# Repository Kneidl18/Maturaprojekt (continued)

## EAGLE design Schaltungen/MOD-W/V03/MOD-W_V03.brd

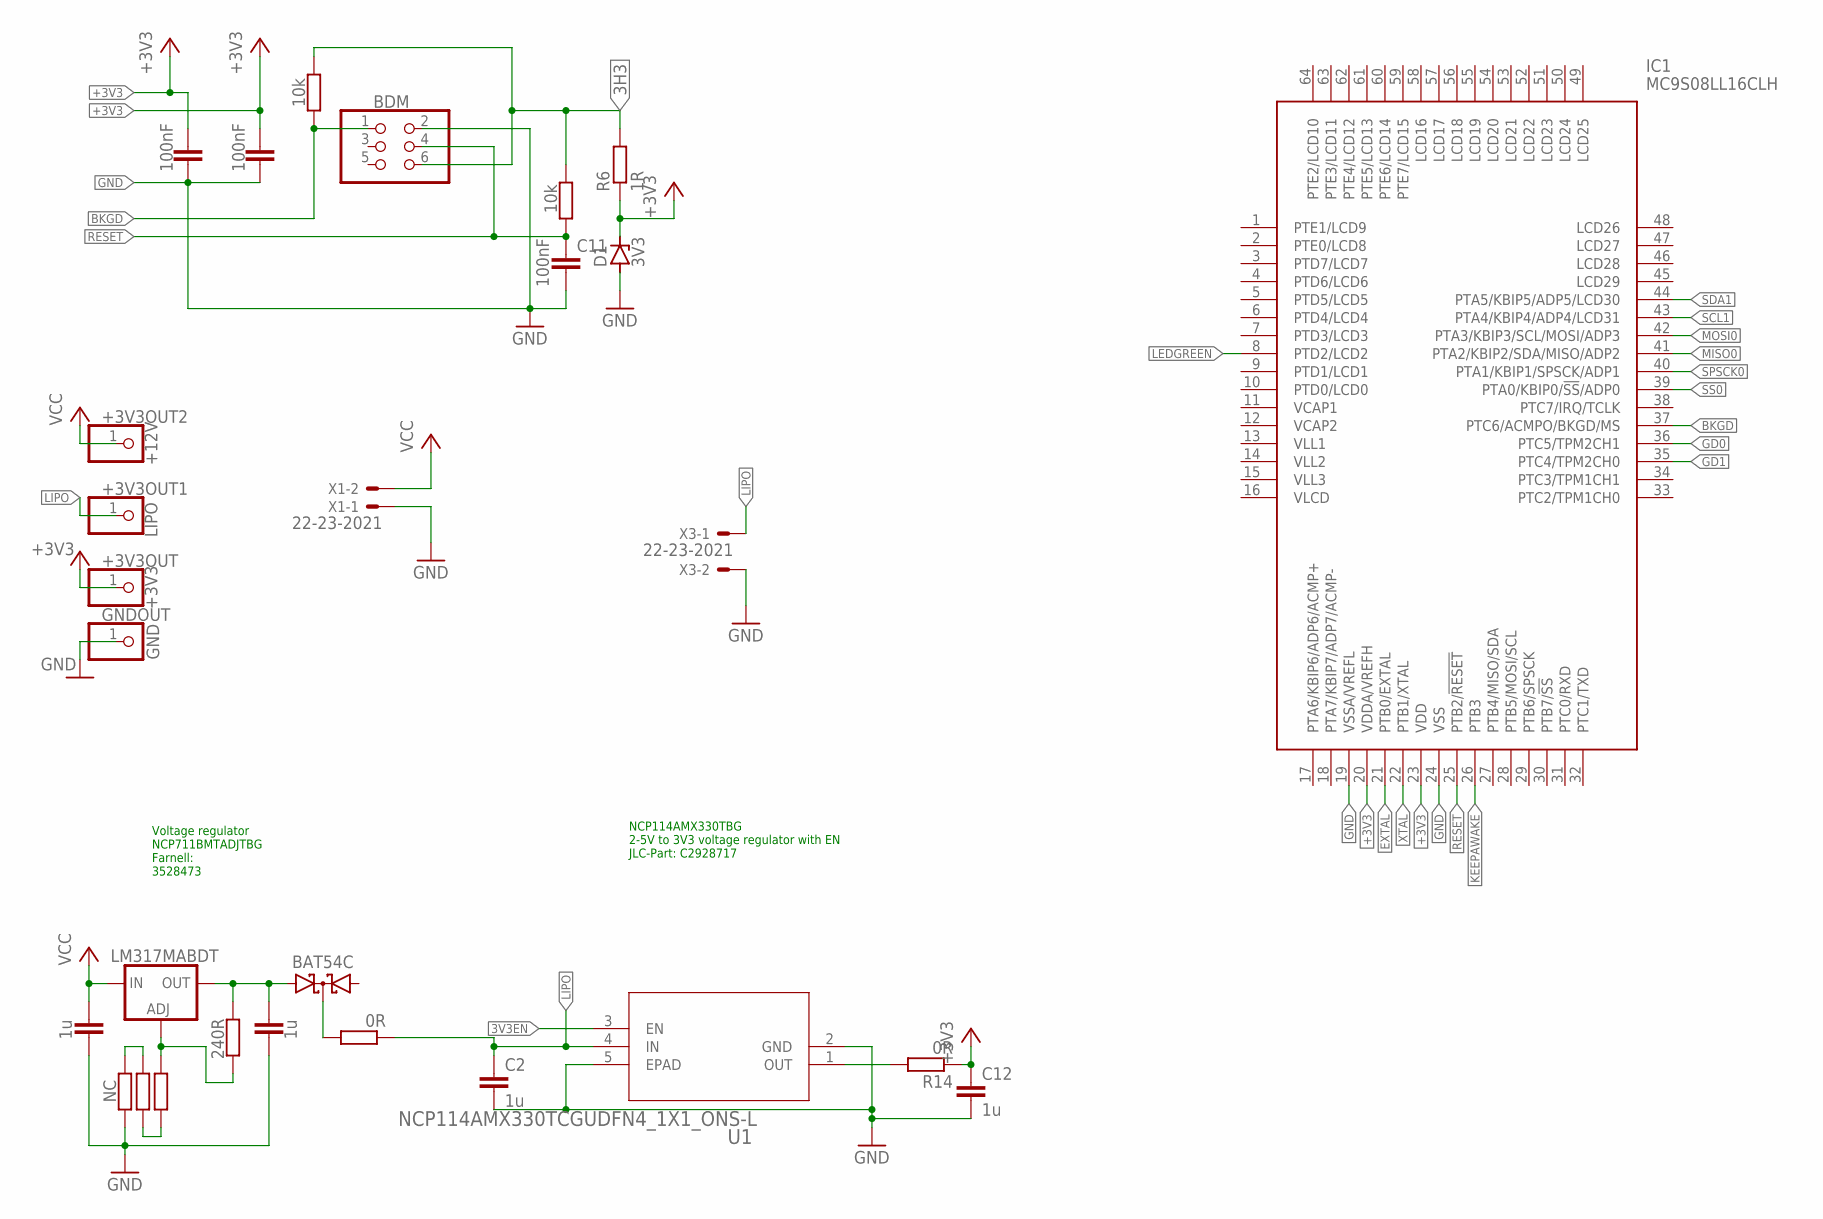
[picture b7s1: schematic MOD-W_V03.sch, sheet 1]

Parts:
+3V3OUT: +3V3; 1X01
+3V3OUT1: LIPO; 1X01
+3V3OUT2: +12V; 1X01
BDM: PINHD-2X3; 2X03
C1, C2, C12, C13: 1u; C0805
C9, C10, C11: 100nF; C0805
D1: 3V3; SOD80C
D7: BAT54C; SOT23
GNDOUT: GND; 1X01
IC1: MC9S08LL16CLH; QFP50P1200X1200X160-64N
IC4: LM317MABDT; DPACK
R2, R18, R19: NC; R0805
R6: 1R; R0805
R7, R14: 0R; R0805
R15: 240R; R0805
R16, R17: 10k; R0805
U1: NCP114AMX330TCGUDFN4_1X1_ONS-L; UDFN4_1X1_ONS-L
X1, X3: 22-23-2021

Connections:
3H3: BDM.6, R6.2, R16.2, R17.2
3V3EN: U1.3 (EN); also elsewhere on the board
+3V3: +3V3OUT.1, C9.1, C10.1, C12.1, D1.C, IC1.20 (VDDA/VREFH), IC1.23 (VDD), R6.1, R14.1; also elsewhere on the board
BKGD: BDM.1, IC1.37 (PTC6/ACMPO/BKGD/MS), R16.1
EXTAL: IC1.21 (PTB0/EXTAL); also elsewhere on the board
GD0: IC1.36 (PTC5/TPM2CH1); also elsewhere on the board
GD1: IC1.35 (PTC4/TPM2CH0); also elsewhere on the board
GND: BDM.2, C1.2, C2.2, C9.2, C10.2, C11.2, C12.2, C13.2, D1.A, GNDOUT.1, IC1.19 (VSSA/VREFL), IC1.24 (VSS), R19.2, U1.2 (GND), U1.5 (EPAD), X1.1, X3.2; also elsewhere on the board
KEEPAWAKE: IC1.26 (PTB3); also elsewhere on the board
LEDGREEN: IC1.8 (PTD2/LCD2); also elsewhere on the board
LIPO: +3V3OUT1.1, C2.1, R7.1, U1.4 (IN), X3.1; also elsewhere on the board
MISO0: IC1.41 (PTA2/KBIP2/SDA/MISO/ADP2); also elsewhere on the board
MOSI0: IC1.42 (PTA3/KBIP3/SCL/MOSI/ADP3); also elsewhere on the board
unnamed: D7.3 (CC), R7.2
unnamed: R14.2, U1.1 (OUT)
unnamed: R2.2, R18.1
unnamed: R2.1, R19.1
unnamed: C1.1, D7.2 (A2), IC4.4 (OUT), R15.2
unnamed: IC4.1 (ADJ), R15.1, R18.2
RESET: BDM.4, C11.1, IC1.25 (PTB2/!RESET), R17.1
SCL1: IC1.43 (PTA4/KBIP4/ADP4/LCD31); also elsewhere on the board
SDA1: IC1.44 (PTA5/KBIP5/ADP5/LCD30); also elsewhere on the board
SPSCK0: IC1.40 (PTA1/KBIP1/SPSCK/ADP1); also elsewhere on the board
SS0: IC1.39 (PTA0/KBIP0/!SS!/ADP0); also elsewhere on the board
VCC: +3V3OUT2.1, C13.1, IC4.3 (IN), X1.2
XTAL: IC1.22 (PTB1/XTAL); also elsewhere on the board

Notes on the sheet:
NCP114AMX330TBG 2-5V to 3V3 voltage regulator with EN JLC-Part: C2928717
Voltage regulator NCP711BMTADJTBG Farnell: 3528473

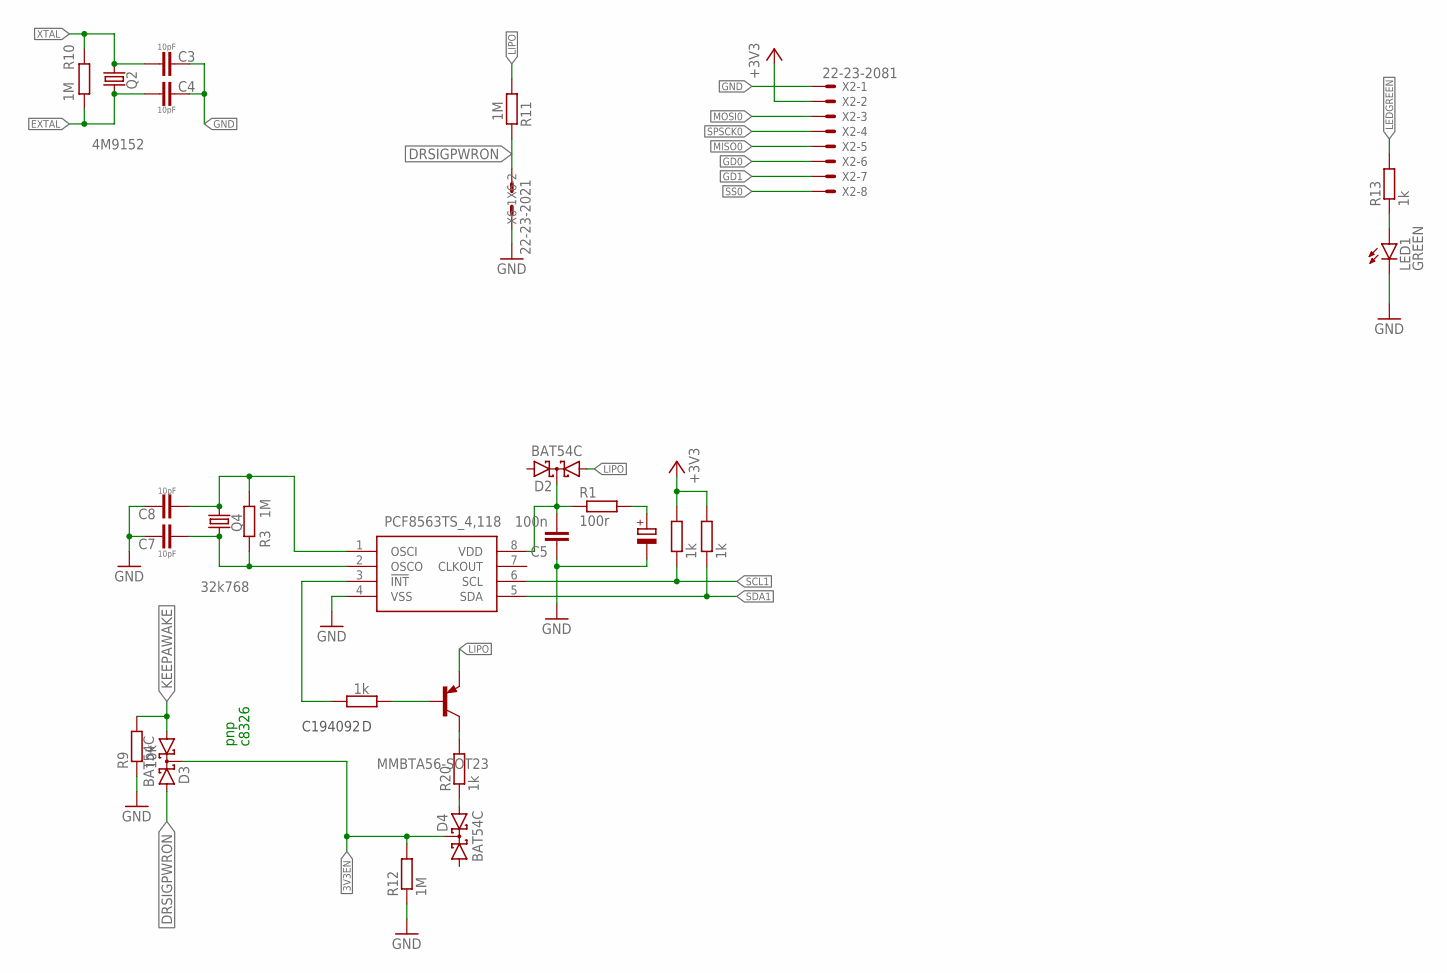
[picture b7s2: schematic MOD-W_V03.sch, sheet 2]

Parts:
C3, C4, C7, C8: 10pF; C0805
C5: 100n; C0805
C6: 100u; PANASONIC_E
D2, D3, D4: BAT54C; SOT23
IC3: PCF8563TS_4,118; SOP65P490X110-8N
LED1: GREEN; CHIP-LED0805
Q2: 4M9152; HC49UP
Q3: MMBTA56-SOT23; SOT23
Q4: 32k768; TC38H
R1: 100r; R0805
R3, R10, R11, R12: 1M; R0805
R4, R5, R8, R13, R20: 1k; R0805
R9: 10k; R0805
X2: 22-23-2081
X6: 22-23-2021

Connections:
3V3EN: D3.3 (CC), D4.3 (CC), R12.2; also elsewhere on the board
+3V3: R4.2, R5.2, X2.2; also elsewhere on the board
DRSIGPWRON: D3.2 (A2), R11.2, X6.1
EXTAL: C4.1, Q2.1, R10.1; also elsewhere on the board
EXTAL1: C8.1, IC3.1 (OSCI), Q4.2, R3.1
GD0: X2.6; also elsewhere on the board
GD1: X2.7; also elsewhere on the board
GND: C3.2, C4.2, C5.1, C6.-, C7.2, C8.2, IC3.4 (VSS), LED1.C, R9.1, R12.1, X2.1, X6.2; also elsewhere on the board
KEEPAWAKE: D3.1 (A1), R9.2; also elsewhere on the board
LEDGREEN: R13.2; also elsewhere on the board
LIPO: D2.1 (A1), Q3.2 (E), R11.1; also elsewhere on the board
MISO0: X2.5; also elsewhere on the board
MOSI0: X2.3; also elsewhere on the board
unnamed: C5.2, D2.3 (CC), IC3.8 (VDD), R1.1
unnamed: C6.+, R1.2
unnamed: IC3.3 (!INT), R8.2
unnamed: Q3.1 (B), R8.1
unnamed: D4.2 (A2), R20.1
unnamed: LED1.A, R13.1
unnamed: Q3.3 (C), R20.2
SCL1: IC3.6 (SCL), R4.1; also elsewhere on the board
SDA1: IC3.5 (SDA), R5.1; also elsewhere on the board
SPSCK0: X2.4; also elsewhere on the board
SS0: X2.8; also elsewhere on the board
XTAL: C3.1, Q2.2, R10.2; also elsewhere on the board
XTAL1: C7.1, IC3.2 (OSCO), Q4.1, R3.2

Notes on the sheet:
c8326
pnp
C194092

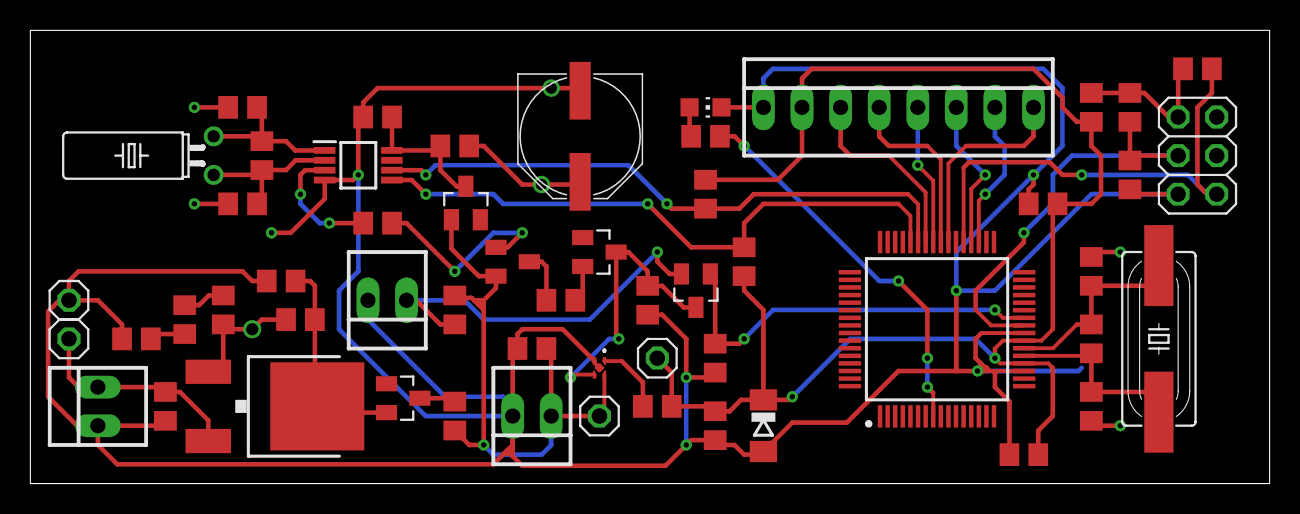
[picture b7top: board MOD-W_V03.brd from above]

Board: 2 copper layers, 81.6 x 29.8 mm, 55 parts (0 on the bottom side), 36 nets.

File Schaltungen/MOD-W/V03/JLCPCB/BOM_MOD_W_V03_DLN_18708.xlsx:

Comment | Designator | Footprint | LCSC Part #（optional）
10pF | C3, C4, C7, C8 | 0805_C | C1785
100nF | C5, C9, C10, C11 | 0805_C | C49678
1u | C1, C2, C12, C13 | 0805_C | C28323
1R | R6 | 0805_R | C25271
100R | R1 | 0805_R | C17408
240R | R15 | 0805_R | C17572
1k | R4, R5, R8, R13, R20 | 0805_R | C17513
10k | R9, R16, R17 | 0805_R | C17414
1M | R3, R10, R11, R12 | 0805_R | C17514
BAT54C | D2, D3, D4, D7 | SOT23 | C37704
LM317 | IC4 | SOT223 | C75510
NCP114AMX330TCG | U1 | UDFN4 | C2928717

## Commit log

2023-01-09 initial commit. The Project is submitted but not finished
2023-06-01 first commit -> website/api/db
2023-06-01 connection to api stable; started to embed image of gui
2024-11-03 Create LICENSE
2024-11-03 add license
2024-11-10 make api accessible in docker container
